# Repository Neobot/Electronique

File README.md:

Electronique
============

For Design of PCB

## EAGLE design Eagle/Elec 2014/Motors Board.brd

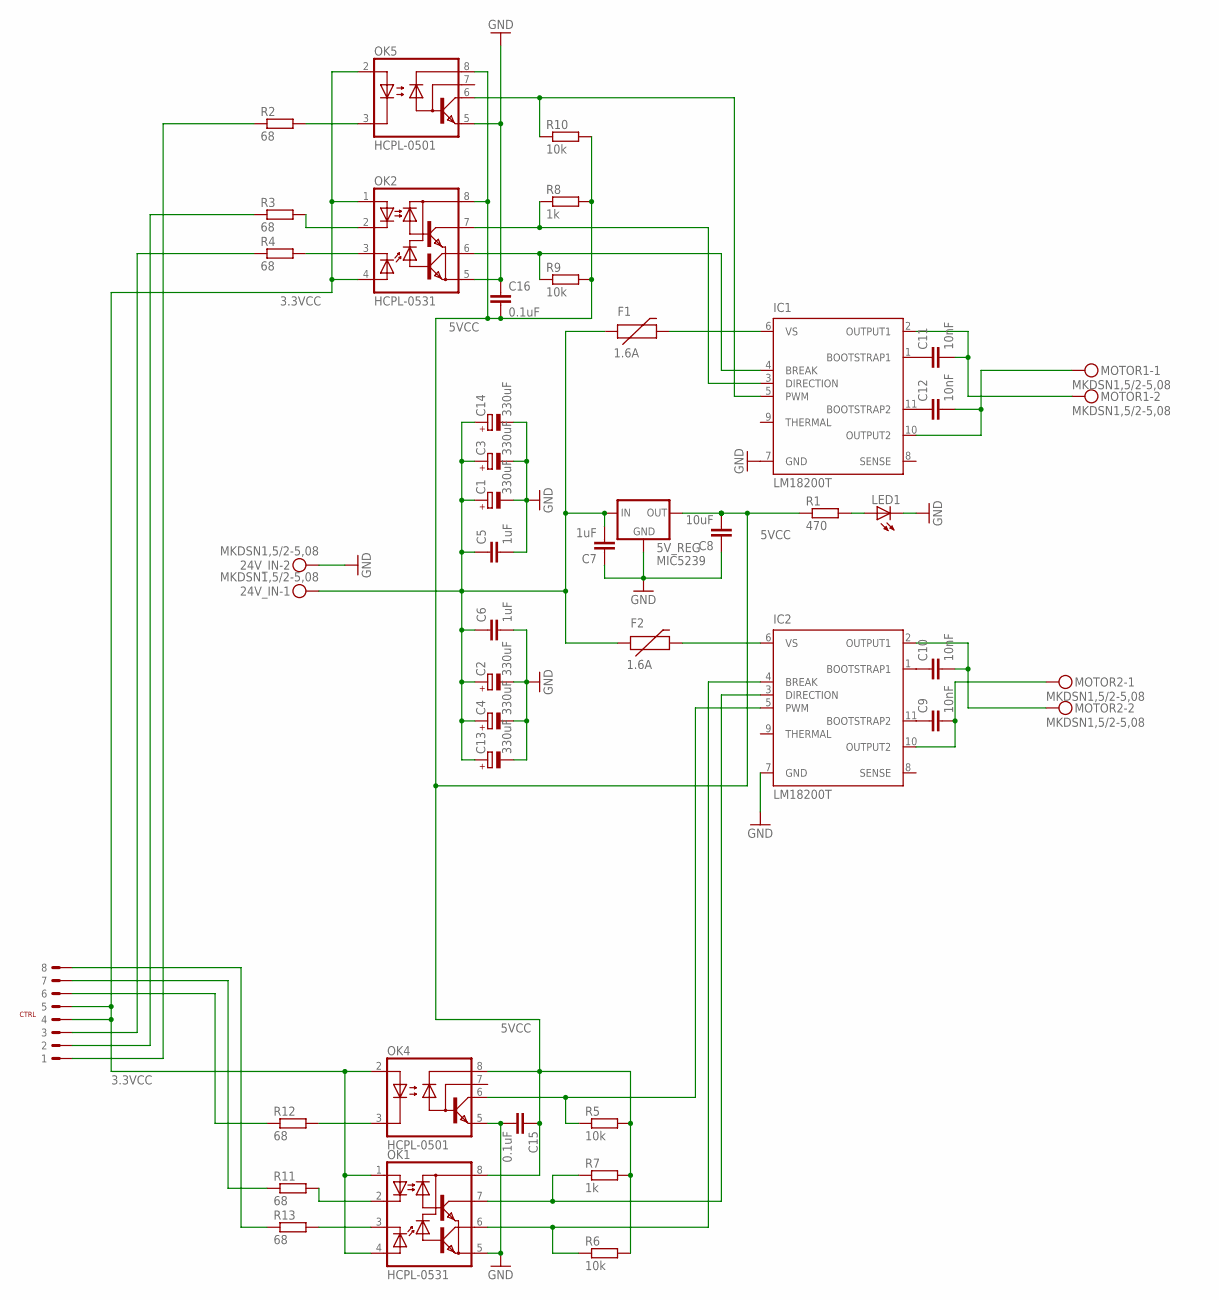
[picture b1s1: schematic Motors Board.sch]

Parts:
5V_REG: MIC5239; SOT223
24V_IN: MKDSN1,5/2-5,08
C1, C2, C3, C4, C13, C14: 330uF; E5-10,5
C5, C6: 1uF; C1206
C7: 1uF; C0805
C8: 10uF; C0805
C9, C10, C11, C12: 10nF; C0603
C15, C16: 0.1uF; C0603
CTRL: 87437-0843
F1, F2: 1.6A; PTC
IC1, IC2: LM18200T; TO-220-11
LED1: LEDCHIP-LED0603; CHIP-LED0603
MOTOR1, MOTOR2: MKDSN1,5/2-5,08
OK1, OK2: HCPL-0531; SOIC8
OK4, OK5: HCPL-0501; SOIC08
R1: 470; R0603
R2, R3, R4, R11, R12, R13: 68; R0603
R5, R6, R9, R10: 10k; R0603
R7, R8: 1k; R0603

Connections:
3.3VCC: CTRL.P$4 (4), CTRL.P$5 (5), OK1.1 (A1), OK1.4 (A2), OK2.1 (A1), OK2.4 (A2), OK4.2 (A), OK5.2 (A)
5VCC: 5V_REG.3 (OUT), C8.2, C15.1, C16.2, OK1.8 (VCC), OK2.8 (VCC), OK4.8 (VCC), OK5.8 (VCC), R1.1, R5.2, R6.2, R7.2, R8.2, R9.2, R10.2
24VIN: 5V_REG.1 (IN), 24V_IN.1, C1.+, C2.+, C3.+, C4.+, C5.1, C6.1, C7.2, C13.+, C14.+, F1.P$1 (1), F2.P$1 (1)
BREAK1: IC1.4 (BREAK), OK2.6 (VO2), R9.1
BREAK1_: CTRL.P$3 (3), R4.1
BREAK2: IC2.4 (BREAK), OK1.6 (VO2), R6.1
BREAK2_: CTRL.P$8 (8), R13.1
DIR1: IC1.3 (DIRECTION), OK2.7 (VO1), R8.1
DIR1_: CTRL.P$2 (2), R3.1
DIR2: IC2.3 (DIRECTION), OK1.7 (VO1), R7.1
DIR2_: CTRL.P$7 (7), R11.1
GND: 5V_REG.2 (GND), 5V_REG.4 (GND), 24V_IN.2, C1.-, C2.-, C3.-, C4.-, C5.2, C6.2, C7.1, C8.1, C13.-, C14.-, C15.2, C16.1, IC1.7 (GND), IC2.7 (GND), LED1.C, OK1.5 (GND), OK2.5 (GND), OK4.5 (GND), OK5.5 (GND)
unnamed: C11.1, IC1.1 (BOOTSTRAP1)
unnamed: C12.2, IC1.10 (OUTPUT2), MOTOR1.1
unnamed: C11.2, IC1.2 (OUTPUT1), MOTOR1.2
unnamed: C9.2, IC2.10 (OUTPUT2), MOTOR2.1
unnamed: LED1.A, R1.2
unnamed: C10.2, IC2.2 (OUTPUT1), MOTOR2.2
unnamed: OK5.3 (C), R2.2
unnamed: OK2.2 (C1), R3.2
unnamed: OK2.3 (C2), R4.2
unnamed: OK1.3 (C2), R13.2
unnamed: OK1.2 (C1), R11.2
unnamed: F1.P$2 (2), IC1.6 (VS)
unnamed: OK4.3 (C), R12.2
unnamed: C12.1, IC1.11 (BOOTSTRAP2)
unnamed: C9.1, IC2.11 (BOOTSTRAP2)
unnamed: C10.1, IC2.1 (BOOTSTRAP1)
unnamed: F2.P$2 (2), IC2.6 (VS)
PWM1: IC1.5 (PWM), OK5.6 (VO), R10.1
PWM1_: CTRL.P$1 (1), R2.1
PWM2: IC2.5 (PWM), OK4.6 (VO), R5.1
PWM2_: CTRL.P$6 (6), R12.1

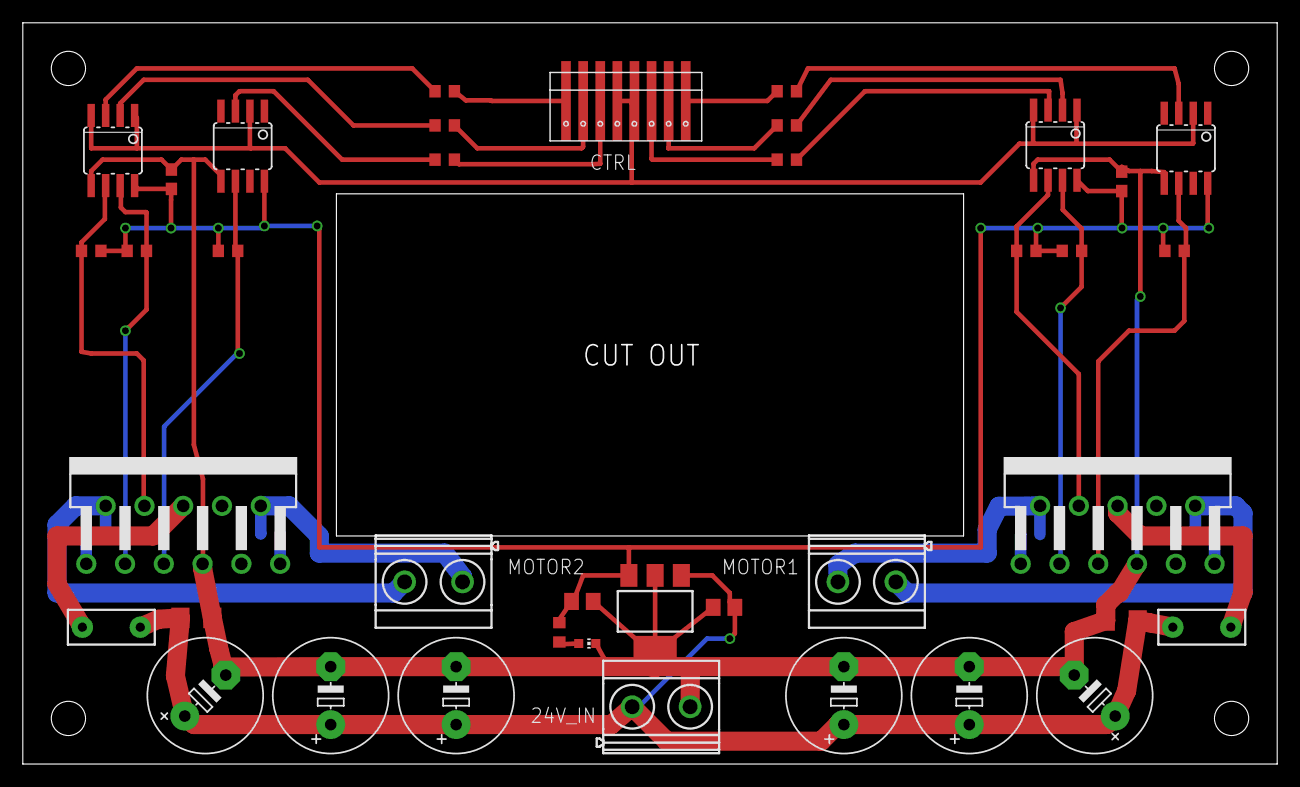
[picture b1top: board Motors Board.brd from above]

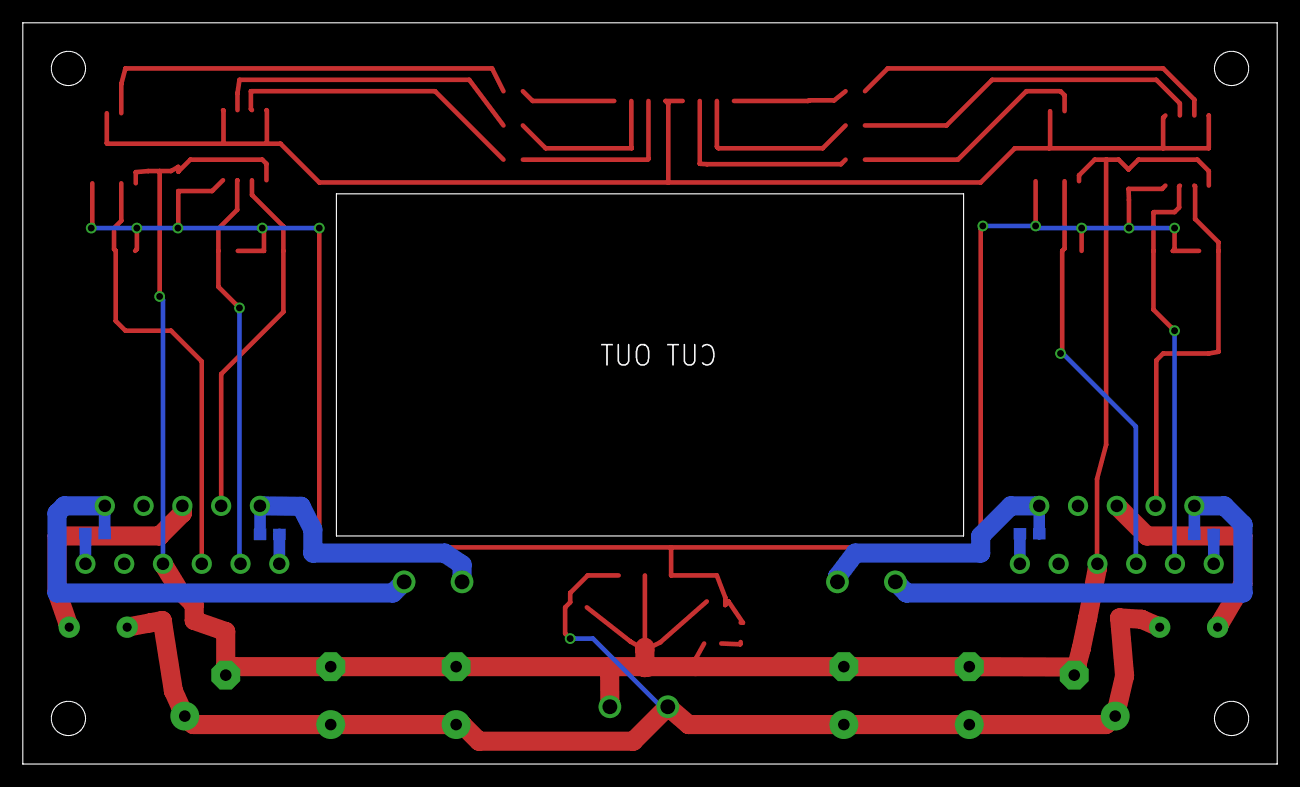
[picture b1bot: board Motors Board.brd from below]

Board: 2 copper layers, 110.0 x 65.0 mm, 43 parts (4 on the bottom side), 33 nets.

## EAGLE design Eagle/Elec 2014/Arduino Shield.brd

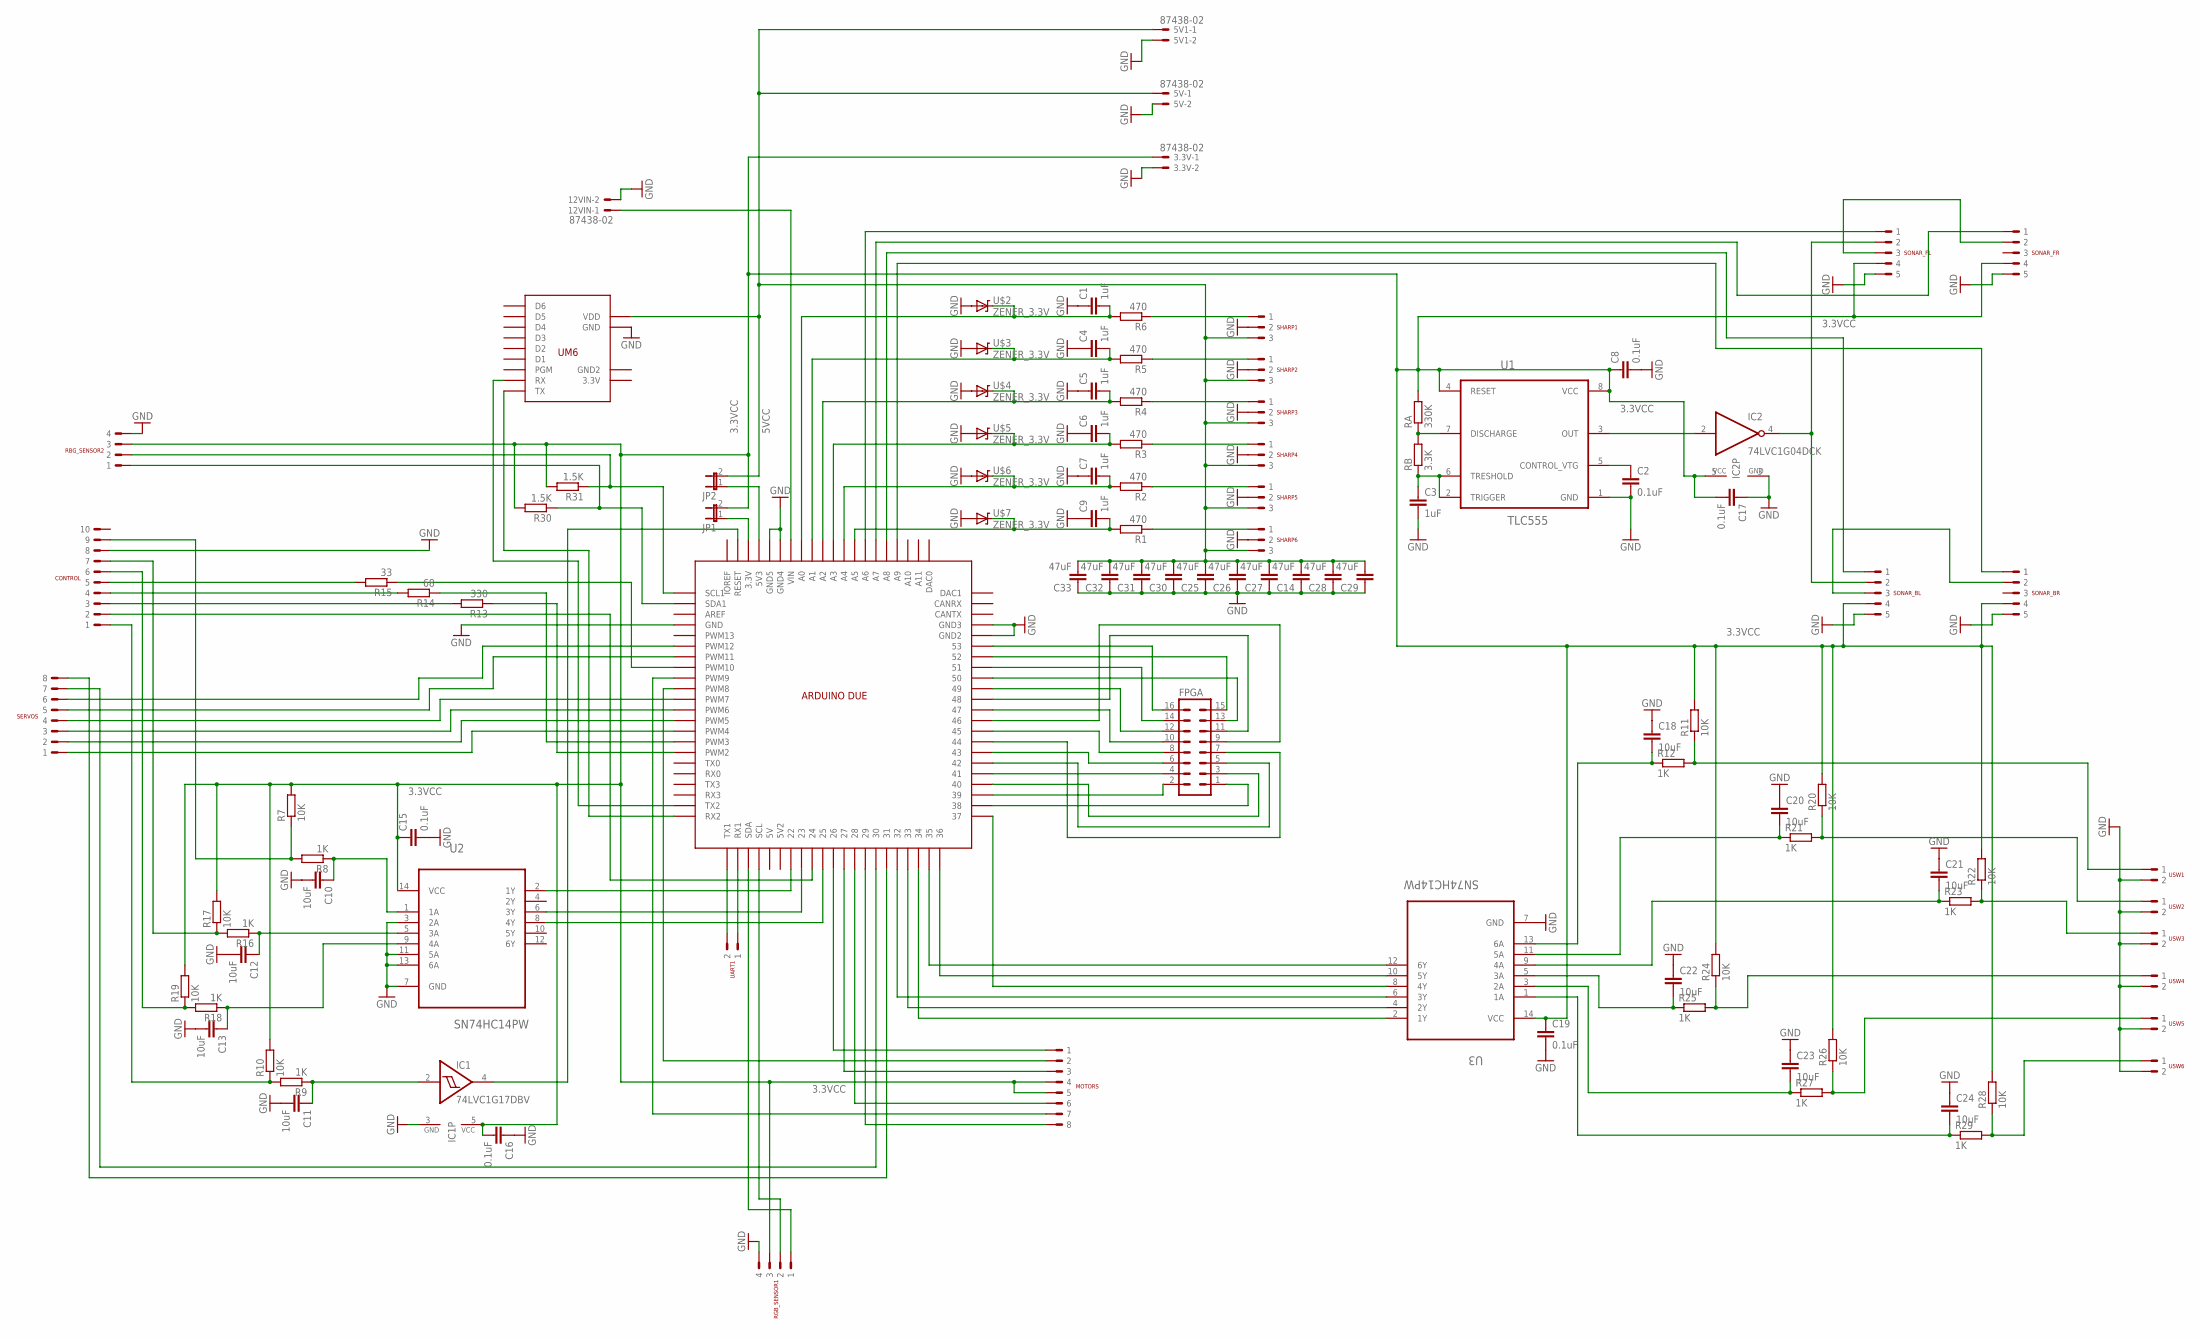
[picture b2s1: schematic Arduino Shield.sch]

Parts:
3.3V, 5V, 5V1, 12VIN: 87438-02
C1, C3, C4, C5, C6, C7, C9: 1uF; C0603
C2, C8, C15, C16, C17, C19: 0.1uF; C0603
C10, C11, C12, C13, C18, C20, C21, C22, C23, C24: 10uF; C0603
C14, C25, C26, C27, C28, C29, C30, C31, C32, C33: 47uF; C1206
CONTROL: 87437-1043
FPGA: ML16
IC1: 74LVC1G17DBV; SOT23-5
IC2: 74LVC1G04DCK; SC70-5
JP1, JP2: JP1E; JP1
MOTORS: 87437-0843
R1, R2, R3, R4, R5, R6: 470; R0603
R7, R10, R11, R17, R19, R20, R22, R24, R26, R28: 10K; R0603
R8, R9, R12, R16, R18, R21, R23, R25, R27, R29: 1K; R0603
R13: 330; R0603
R14: 68; R0603
R15: 33; R0603
R30, R31: 1.5K; R0603
RA: 330K; R0603
RB: 3.3K; R0603
RBG_SENSOR2: 87437-0443
RGB_SENSOR1: 87437-0443
SERVOS: 87437-0843
SHARP1, SHARP2, SHARP3, SHARP4, SHARP5, SHARP6: 87437-0343
SONAR_BL: 87437-0543
SONAR_BR: 87437-0543
SONAR_FL: 87437-0543
SONAR_FR: 87437-0543
U1: TLC555; SOIC127P600X175-8N
U2, U3: SN74HC14PW; SOP65P640X120-14N
U$1: ARDUINO-DUE
U$2, U$3, U$4, U$5, U$6, U$7: ZENER_3.3V; SOD-323
UART1: 87437-0243
UM6: UM6
USW1, USW2, USW3, USW4, USW5, USW6: 87437-0243

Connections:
3.3VCC: 3.3V.1, C8.1, C15.1, C16.2, C17.2, C19.1, IC1.5 (VCC), IC2.5 (VCC), JP1.2, MOTORS.P$4 (4), MOTORS.P$5 (5), R7.2, R10.2, R11.2, R17.2, R19.2, R20.2, R22.2, R24.2, R26.2, R28.2, R30.2, R31.2, RA.2, RBG_SENSOR2.P$3 (3), RGB_SENSOR1.P$3 (3), SONAR_BL.P$4 (4), SONAR_BR.P$4 (4), SONAR_FL.P$4 (4), SONAR_FR.P$4 (4), U1.4 (RESET), U1.8 (VCC), U2.14 (VCC), U3.14 (VCC)
5VCC: 5V.1, 5V1.1, C14.2, C25.2, C26.2, C27.2, C28.2, C29.2, C30.2, C31.2, C32.2, C33.2, JP2.2, SHARP1.P$3 (3), SHARP2.P$3 (3), SHARP3.P$3 (3), SHARP4.P$3 (3), SHARP5.P$3 (3), SHARP6.P$3 (3), UM6.P$10 (VDD)
12VIN: 12VIN.1, U$1.VIN
BLUE: R15.1, U$1.PWM10
BTN1: U2.6 (3Y), U$1.23
BTN2: U2.8 (4Y), U$1.25
BUT1: CONTROL.P$7 (7), R16.2, R17.1
BUT2: CONTROL.P$6 (6), R18.2, R19.1
COLOR: CONTROL.P$2 (2), U$1.24
GND: 3.3V.2, 5V.2, 5V1.2, 12VIN.2, C1.1, C2.2, C3.2, C4.1, C5.1, C6.1, C7.1, C8.2, C9.1, C10.2, C11.2, C12.2, C13.2, C14.1, C15.2, C16.1, C17.1, C18.1, C19.2, C20.1, C21.1, C22.1, C23.1, C24.1, C25.1, C26.1, C27.1, C28.1, C29.1, C30.1, C31.1, C32.1, C33.1, CONTROL.P$8 (8), IC1.3 (GND), IC2.3 (GND), RBG_SENSOR2.P$4 (4), RGB_SENSOR1.P$4 (4), SHARP1.P$2 (2), SHARP2.P$2 (2), SHARP3.P$2 (2), SHARP4.P$2 (2), SHARP5.P$2 (2), SHARP6.P$2 (2), SONAR_BL.P$5 (5), SONAR_BR.P$5 (5), SONAR_FL.P$5 (5), SONAR_FR.P$5 (5), U1.1 (GND), U2.3 (2A), U2.7 (GND), U2.11 (5A), U2.13 (6A), U3.7 (GND), U$1.GND, U$1.GND2, U$1.GND3, U$1.GND4, U$1.GND5, U$2.2 (A), U$3.2 (A), U$4.2 (A), U$5.2 (A), U$6.2 (A), U$7.2 (A), UM6.P$11 (GND), USW1.P$2 (2), USW2.P$2 (2), USW3.P$2 (2), USW4.P$2 (2), USW5.P$2 (2), USW6.P$2 (2)
GREEN: R14.1, U$1.PWM3
JACK: U2.2 (1Y), U$1.22
MOTOR1_BREAK: MOTORS.P$6 (6), U$1.28
MOTOR1_DIR: MOTORS.P$7 (7), U$1.PWM9
MOTOR1_PWM: MOTORS.P$8 (8), U$1.29
MOTOR2_BREAK: MOTORS.P$1 (1), U$1.26
MOTOR2_DIR: MOTORS.P$2 (2), U$1.PWM8
MOTOR2_PWM: MOTORS.P$3 (3), U$1.27
unnamed: JP1.1, U$1.3.3V
unnamed: C12.1, R16.1, U2.5 (3A)
unnamed: SERVOS.P$1 (1), U$1.PWM4
unnamed: SERVOS.P$2 (2), U$1.PWM5
unnamed: SERVOS.P$3 (3), U$1.PWM6
unnamed: SERVOS.P$4 (4), U$1.PWM7
unnamed: IC1.4 (O), U$1.RESET
unnamed: JP2.1, U$1.5V3
unnamed: R11.1, R12.2, USW1.P$1 (1)
unnamed: C18.2, R12.1, U3.13 (6A)
unnamed: C13.1, R18.1, U2.9 (4A)
unnamed: SERVOS.P$5 (5), U$1.PWM11
unnamed: SERVOS.P$6 (6), U$1.PWM12
unnamed: SERVOS.P$7 (7), U$1.30
unnamed: CONTROL.P$5 (5), R15.2
unnamed: CONTROL.P$4 (4), R14.2
unnamed: CONTROL.P$3 (3), R13.2
unnamed: SERVOS.P$8 (8), U$1.31
unnamed: R20.1, R21.2, USW2.P$1 (1)
unnamed: C20.2, R21.1, U3.11 (5A)
unnamed: R22.1, R23.2, USW3.P$1 (1)
unnamed: C21.2, R23.1, U3.9 (4A)
unnamed: R24.1, R25.2, USW4.P$1 (1)
unnamed: C22.2, R25.1, U3.5 (3A)
unnamed: R26.1, R27.2, USW5.P$1 (1)
unnamed: C23.2, R27.1, U3.3 (2A)
unnamed: CONTROL.P$9 (9), R7.1, R8.2
unnamed: R28.1, R29.2, USW6.P$1 (1)
unnamed: C24.2, R29.1, U3.1 (1A)
unnamed: C3.1, RB.1, U1.2 (TRIGGER), U1.6 (TRESHOLD)
unnamed: C2.1, U1.5 (CONTROL_VTG)
unnamed: RA.1, RB.2, U1.7 (DISCHARGE)
unnamed: IC2.2 (I), U1.3 (OUT)
unnamed: SONAR_FL.P$3 (3), SONAR_FR.P$2 (2)
unnamed: SONAR_BL.P$3 (3), SONAR_BR.P$2 (2)
unnamed: FPGA.1, U$1.38
unnamed: IC2.4 (O), SONAR_BL.P$2 (2), SONAR_FL.P$2 (2)
unnamed: FPGA.2, U$1.39
unnamed: FPGA.3, U$1.40
unnamed: FPGA.4, U$1.41
unnamed: FPGA.5, U$1.42
unnamed: FPGA.6, U$1.43
unnamed: FPGA.7, U$1.44
unnamed: FPGA.8, U$1.45
unnamed: FPGA.9, U$1.46
unnamed: FPGA.10, U$1.47
unnamed: FPGA.11, U$1.48
unnamed: FPGA.12, U$1.49
unnamed: FPGA.13, U$1.50
unnamed: FPGA.14, U$1.51
unnamed: FPGA.15, U$1.52
unnamed: FPGA.16, U$1.53
unnamed: R5.1, SHARP2.P$1 (1)
unnamed: R4.1, SHARP3.P$1 (1)
unnamed: R3.1, SHARP4.P$1 (1)
unnamed: R2.1, SHARP5.P$1 (1)
unnamed: R1.1, SHARP6.P$1 (1)
unnamed: C10.1, R8.1, U2.1 (1A)
unnamed: R6.1, SHARP1.P$1 (1)
unnamed: C11.1, IC1.2 (I), R9.1
RED: R13.1, U$1.PWM2
RST: CONTROL.P$1 (1), R9.2, R10.1
RX1: U$1.RX1, UART1.P$1 (1)
SCL: RGB_SENSOR1.P$2 (2), U$1.SCL
SCL1: R31.1, RBG_SENSOR2.P$2 (2), U$1.SCL1
SDA: RGB_SENSOR1.P$1 (1), U$1.SDA
SDA1: R30.1, RBG_SENSOR2.P$1 (1), U$1.SDA1
SHARP1: C1.2, R6.2, U$1.A0, U$2.1 (C)
SHARP2: C4.2, R5.2, U$1.A1, U$3.1 (C)
SHARP3: C5.2, R4.2, U$1.A2, U$4.1 (C)
SHARP4: C6.2, R3.2, U$1.A3, U$5.1 (C)
SHARP5: C7.2, R2.2, U$1.A4, U$6.1 (C)
SHARP6: C9.2, R1.2, U$1.A5, U$7.1 (C)
SONAR_BL: SONAR_BL.P$1 (1), U$1.A8
SONAR_BR: SONAR_BR.P$1 (1), U$1.A9
SONAR_FL: SONAR_FL.P$1 (1), U$1.A6
SONAR_FR: SONAR_FR.P$1 (1), U$1.A7
TX1: U$1.TX1, UART1.P$2 (2)
UM6_RX: U$1.TX2, UM6.P$2 (RX)
UM6_TX: U$1.RX2, UM6.P$1 (TX)
USW1: U3.2 (1Y), U$1.34
USW2: U3.4 (2Y), U$1.33
USW3: U3.6 (3Y), U$1.32
USW4: U3.8 (4Y), U$1.37
USW5: U3.10 (5Y), U$1.36
USW6: U3.12 (6Y), U$1.35

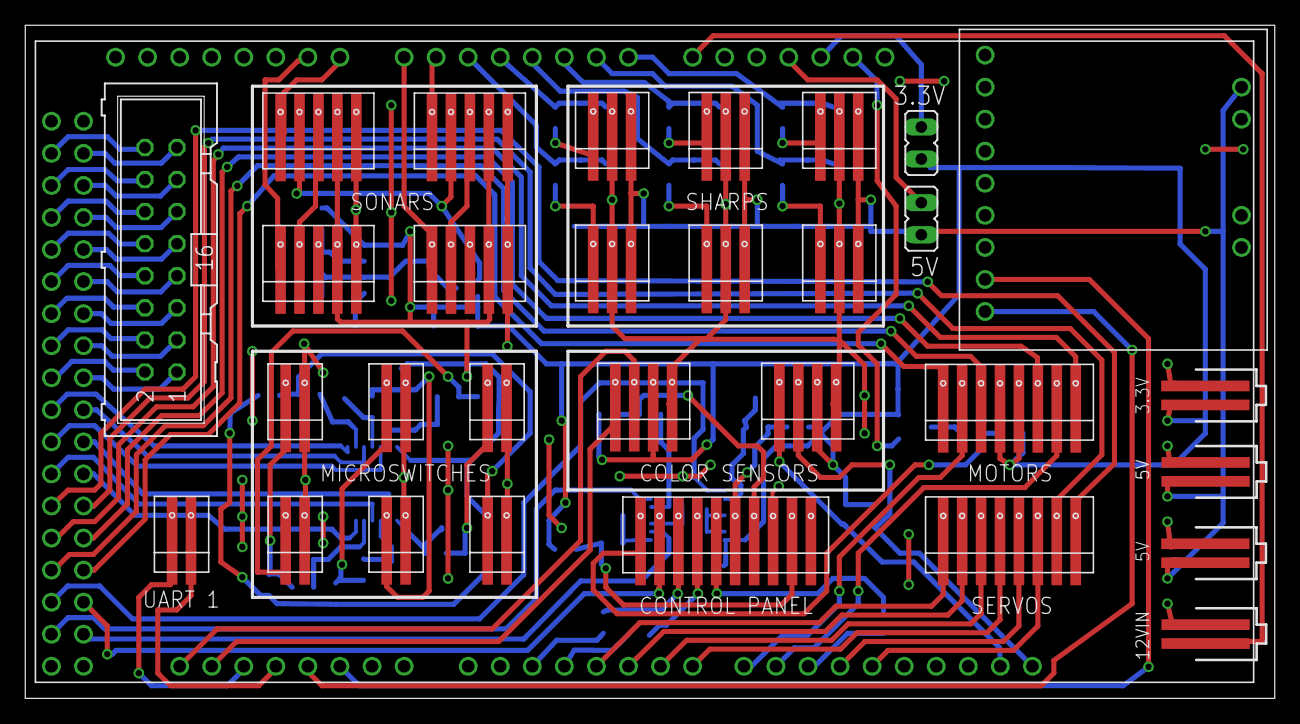
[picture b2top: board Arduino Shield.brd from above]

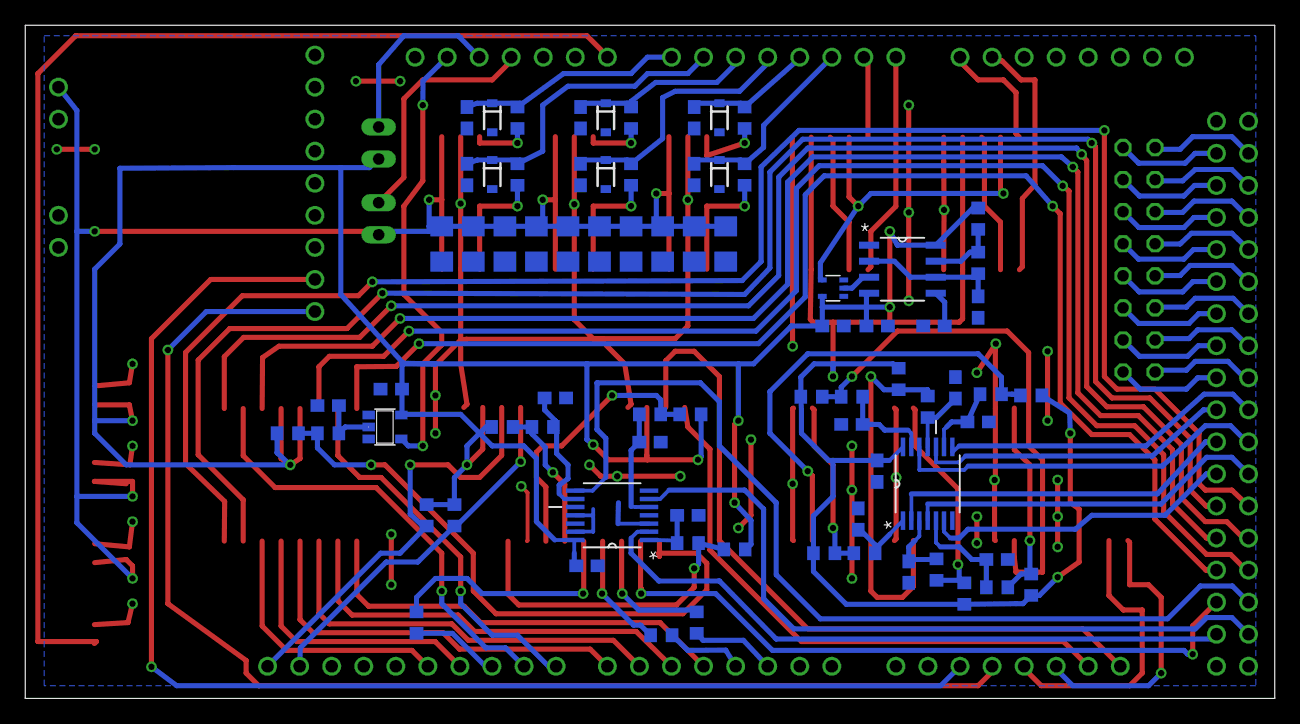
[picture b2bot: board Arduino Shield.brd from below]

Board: 2 copper layers, 99.0 x 53.3 mm, 108 parts (77 on the bottom side), 104 nets.

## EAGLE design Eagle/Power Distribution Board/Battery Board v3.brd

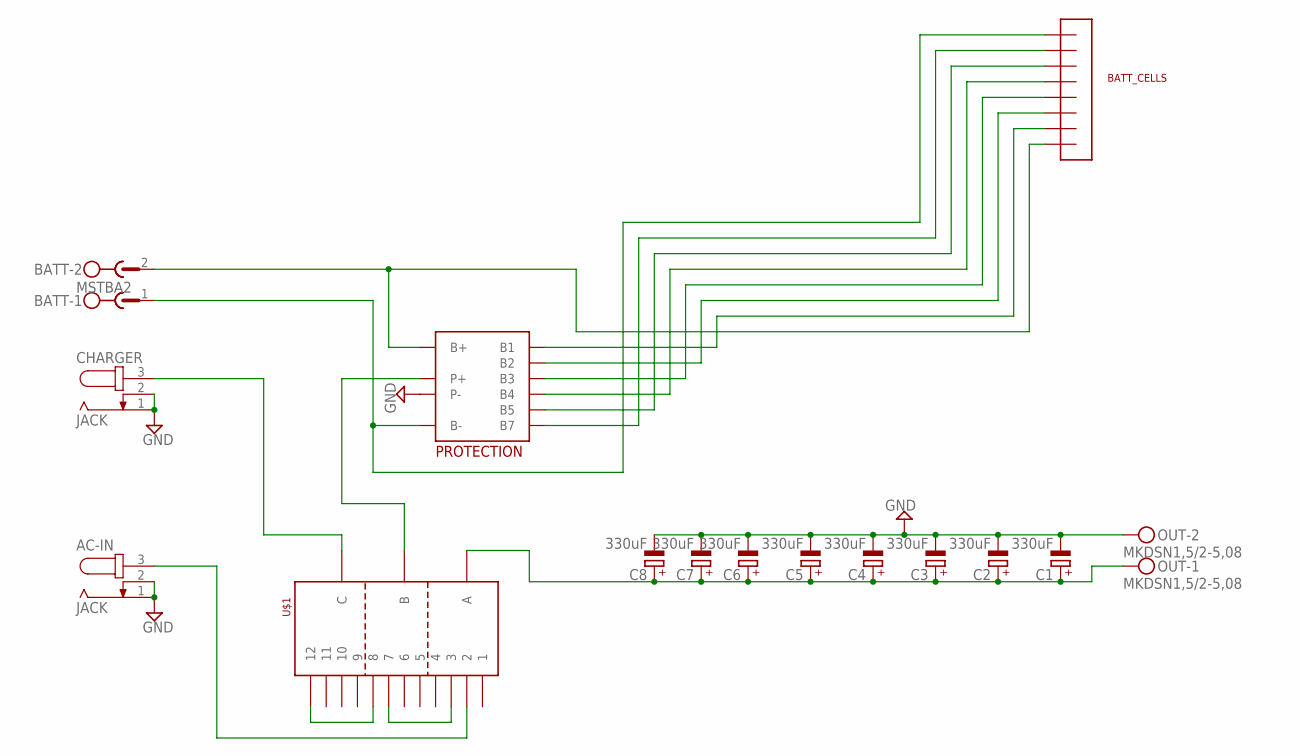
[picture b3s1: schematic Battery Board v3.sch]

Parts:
AC-IN: JACK
BATT: MSTBA2
BATT_CELLS: JST-XH-8; 8PIN-2.5MM
C1, C2, C3, C4, C5, C6, C7, C8: 330uF; E5-10,5
CHARGER: JACK
OUT: MKDSN1,5/2-5,08
PROTECTION: BMS-LIFEPO4-7S
U$1: CK1026

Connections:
B1: BATT_CELLS.P$7, PROTECTION.B1
B2: BATT_CELLS.P$6, PROTECTION.B2
B3: BATT_CELLS.P$5, PROTECTION.B3
B4: BATT_CELLS.P$4, PROTECTION.B4
B5: BATT_CELLS.P$3, PROTECTION.B5
B7: BATT_CELLS.P$2, PROTECTION.B7
B+: BATT.2, BATT_CELLS.P$8, PROTECTION.B+
B-: BATT.1, BATT_CELLS.P$1, PROTECTION.B-
GND: AC-IN.1, AC-IN.2, C1.-, C2.-, C3.-, C4.-, C5.-, C6.-, C7.-, C8.-, CHARGER.1, CHARGER.2, OUT.2, PROTECTION.P-
unnamed: C1.+, C2.+, C3.+, C4.+, C5.+, C6.+, C7.+, C8.+, OUT.1, U$1.A
unnamed: AC-IN.3, U$1.2
unnamed: PROTECTION.P+, U$1.B
unnamed: U$1.3, U$1.7
unnamed: U$1.8, U$1.12
unnamed: CHARGER.3, U$1.C

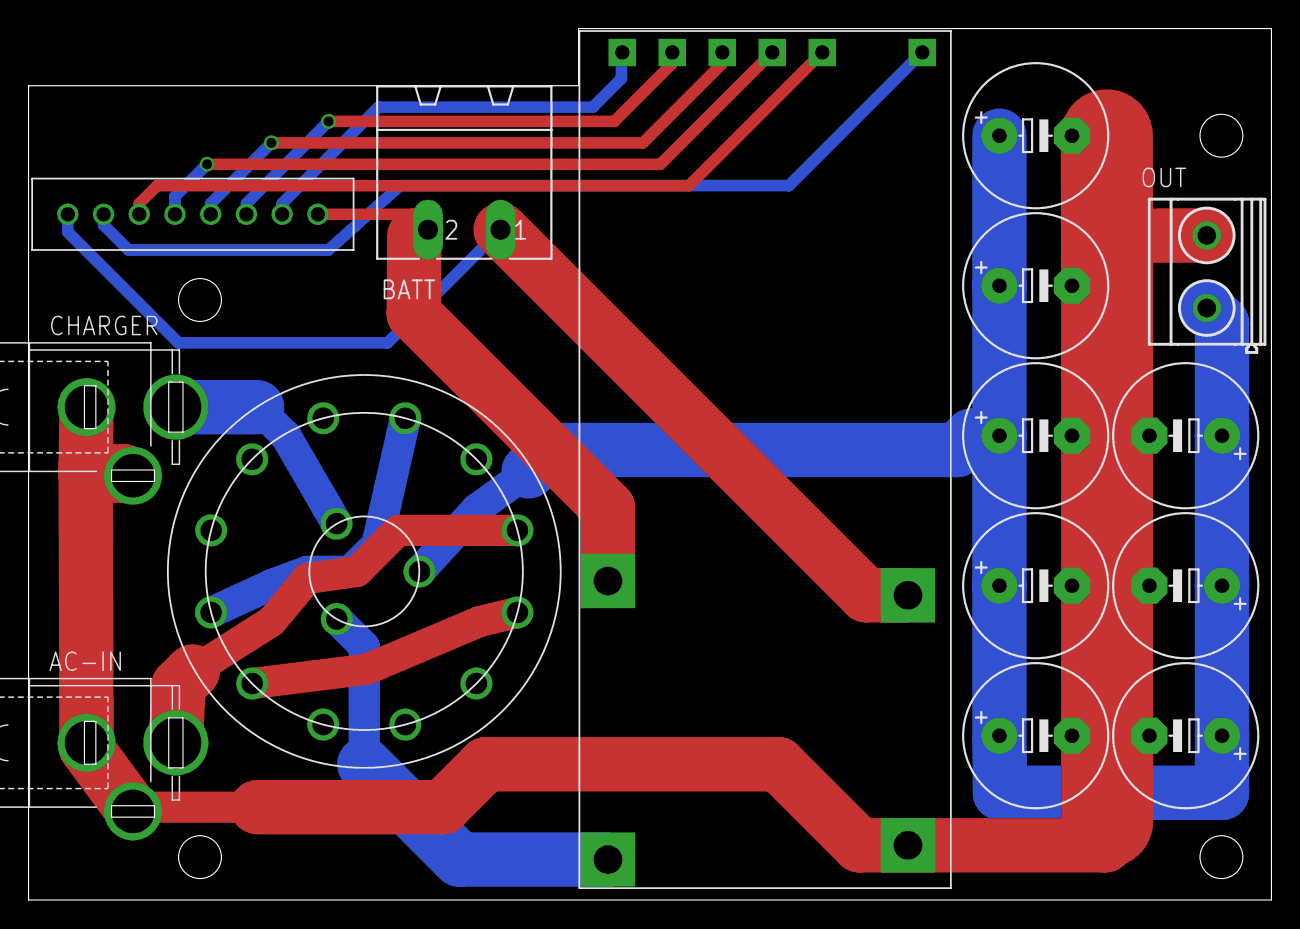
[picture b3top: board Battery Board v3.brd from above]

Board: 2 copper layers, 87.0 x 61.0 mm, 15 parts (0 on the bottom side), 15 nets.

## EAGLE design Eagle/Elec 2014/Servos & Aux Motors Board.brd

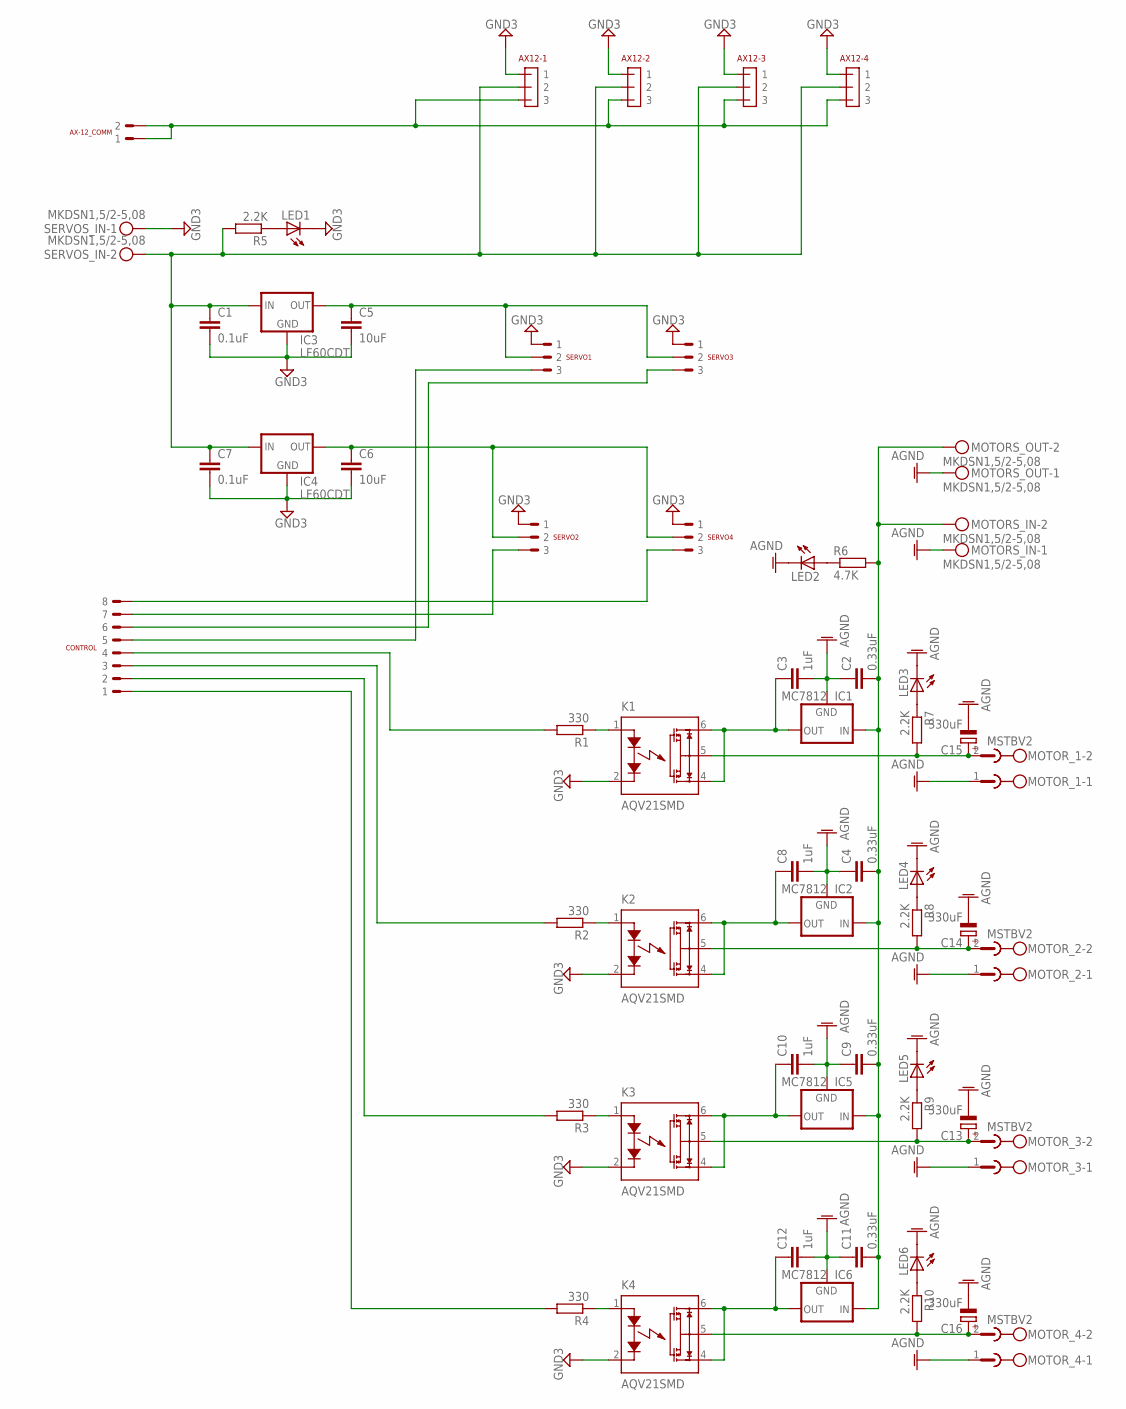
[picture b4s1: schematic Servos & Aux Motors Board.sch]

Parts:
AX12-1, AX12-2, AX12-3, AX12-4: 22-03-5035
AX-12_COMM: 87437-0243
C1, C7: 0.1uF; C0603
C2, C4, C9, C11: 0.33uF; C0805
C3, C8, C10, C12: 1uF; C0805
C5, C6: 10uF; C0805
C13, C14, C15, C16: 330uF; E3,5-8
CONTROL: 87437-0843
IC1, IC2, IC5, IC6: MC7812; DPACK
IC3, IC4: LF60CDT; DPACK
K1, K2, K3, K4: AQV21SMD; DIL06SMD
LED1, LED2, LED3, LED4, LED5, LED6: LEDCHIP-LED0603; CHIP-LED0603
MOTORS_IN: MKDSN1,5/2-5,08
MOTORS_OUT: MKDSN1,5/2-5,08
MOTOR_1, MOTOR_2, MOTOR_3, MOTOR_4: MSTBV2
R1, R2, R3, R4: 330; R0603
R5, R7, R8, R9, R10: 2.2K; R0805
R6: 4.7K; R1206
SERVO1, SERVO2, SERVO3, SERVO4: 87437-0343
SERVOS_IN: MKDSN1,5/2-5,08

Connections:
24VIN: C2.2, C4.2, C9.2, C11.2, IC1.1 (IN), IC2.1 (IN), IC5.1 (IN), IC6.1 (IN), MOTORS_IN.2, MOTORS_OUT.2, R6.2
AGND: C2.1, C3.2, C4.1, C8.2, C9.1, C10.2, C11.1, C12.2, C13.-, C14.-, C15.-, C16.-, IC1.4 (GND), IC2.4 (GND), IC5.4 (GND), IC6.4 (GND), LED2.C, LED3.C, LED4.C, LED5.C, LED6.C, MOTORS_IN.1, MOTORS_OUT.1, MOTOR_1.1, MOTOR_2.1, MOTOR_3.1, MOTOR_4.1
GND3: AX12-1.P$1 (1), AX12-2.P$1 (1), AX12-3.P$1 (1), AX12-4.P$1 (1), C1.2, C5.2, C6.2, C7.2, IC3.4 (GND), IC4.4 (GND), K1.2 (K), K2.2 (K), K3.2 (K), K4.2 (K), LED1.C, SERVO1.P$1 (1), SERVO2.P$1 (1), SERVO3.P$1 (1), SERVO4.P$1 (1), SERVOS_IN.1
MOTOR1: C15.+, K1.5 (S), MOTOR_1.2, R7.2
MOTOR1_CTRL: K1.1 (A), R1.1
MOTOR2: C14.+, K2.5 (S), MOTOR_2.2, R8.2
MOTOR2_CTRL: K2.1 (A), R2.1
MOTOR3: C13.+, K3.5 (S), MOTOR_3.2, R9.2
MOTOR3_CTRL: K3.1 (A), R3.1
MOTOR4: C16.+, K4.5 (S), MOTOR_4.2, R10.2
MOTOR4_CTRL: K4.1 (A), R4.1
unnamed: CONTROL.P$4 (4), R1.2
unnamed: LED1.A, R5.1
unnamed: C3.1, IC1.3 (OUT), K1.4 (D2), K1.6 (D1)
unnamed: LED2.A, R6.1
unnamed: LED3.A, R7.1
unnamed: LED4.A, R8.1
unnamed: C8.1, IC2.3 (OUT), K2.4 (D2), K2.6 (D1)
unnamed: LED5.A, R9.1
unnamed: CONTROL.P$3 (3), R2.2
unnamed: LED6.A, R10.1
unnamed: C10.1, IC5.3 (OUT), K3.4 (D2), K3.6 (D1)
unnamed: C12.1, IC6.3 (OUT), K4.4 (D2), K4.6 (D1)
unnamed: CONTROL.P$1 (1), R4.2
unnamed: CONTROL.P$2 (2), R3.2
unnamed: CONTROL.P$5 (5), SERVO1.P$3 (3)
unnamed: CONTROL.P$6 (6), SERVO3.P$3 (3)
unnamed: CONTROL.P$7 (7), SERVO2.P$3 (3)
unnamed: C6.1, IC4.3 (OUT), SERVO2.P$2 (2), SERVO4.P$2 (2)
unnamed: CONTROL.P$8 (8), SERVO4.P$3 (3)
unnamed: C5.1, IC3.3 (OUT), SERVO1.P$2 (2), SERVO3.P$2 (2)
RXTX: AX12-1.P$3 (3), AX12-2.P$3 (3), AX12-3.P$3 (3), AX12-4.P$3 (3), AX-12_COMM.P$1 (1), AX-12_COMM.P$2 (2)
SERVO_IN: AX12-1.P$2 (2), AX12-2.P$2 (2), AX12-3.P$2 (2), AX12-4.P$2 (2), C1.1, C7.1, IC3.1 (IN), IC4.1 (IN), R5.2, SERVOS_IN.2

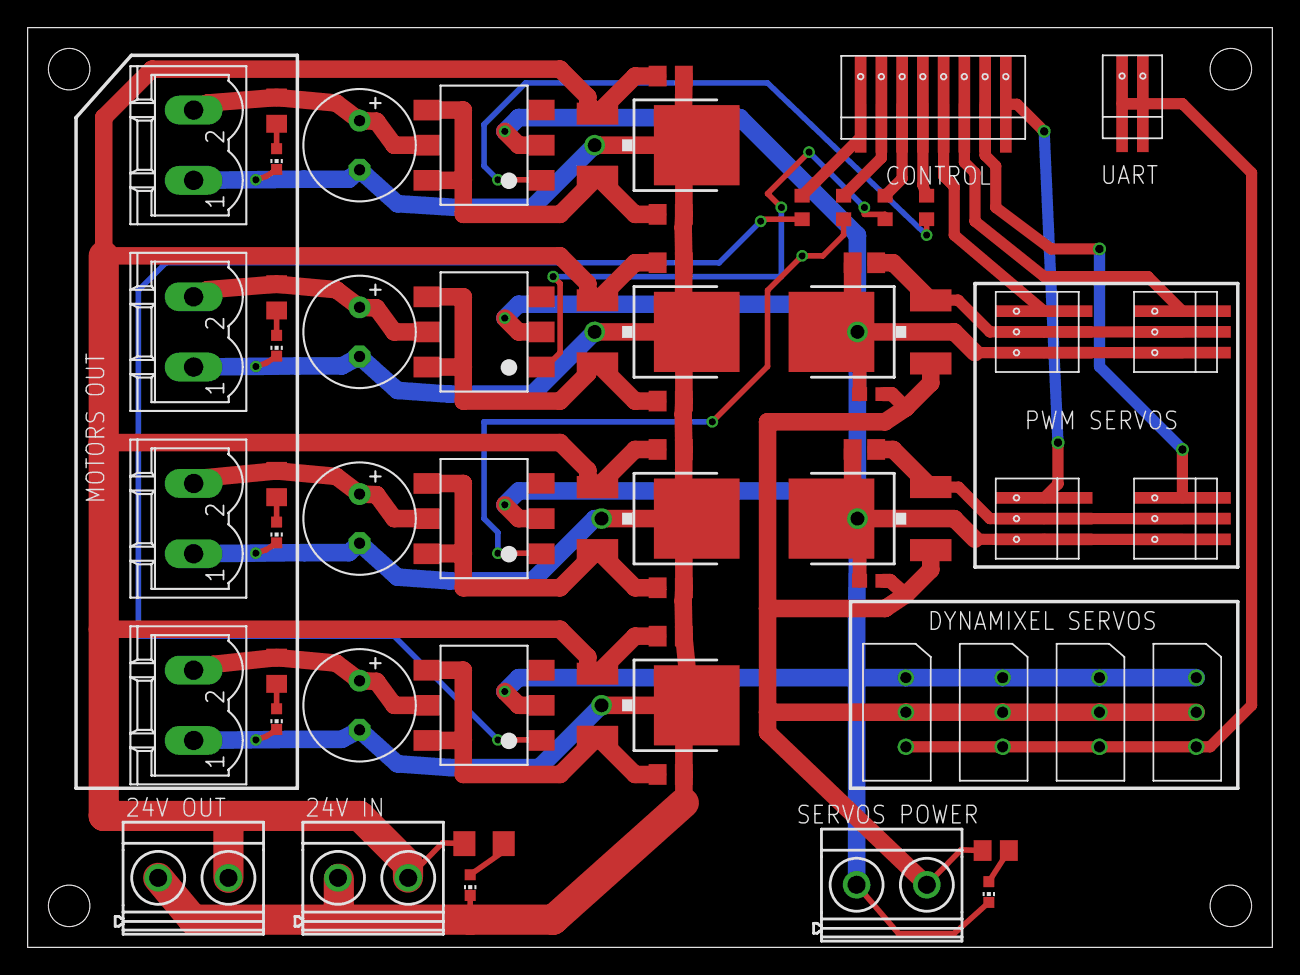
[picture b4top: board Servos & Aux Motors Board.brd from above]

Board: 2 copper layers, 90.0 x 66.5 mm, 59 parts (0 on the bottom side), 33 nets.

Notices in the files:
parts and their libraries:
SparkFun: Licensing: CC v3.0 Share-Alike You are welcome to use this library for commercial purposes.
